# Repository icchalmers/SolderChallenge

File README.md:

# Solder Challenge

The Solder Challenge is a derivative of the [Solder Challenge by Rick Pennen](https://workspace.circuitmaker.com/Projects/Details/Rick-Pannen/Soldering-Challenge).
It's been updated to favour surface mount components and tweaked to parts I could easily source on RS.

# Licence

The project is currently licensed under a CC BY-NC-SA licence, as per the original project. Hopefully I'll get permission to remove the NC clause from the original author.

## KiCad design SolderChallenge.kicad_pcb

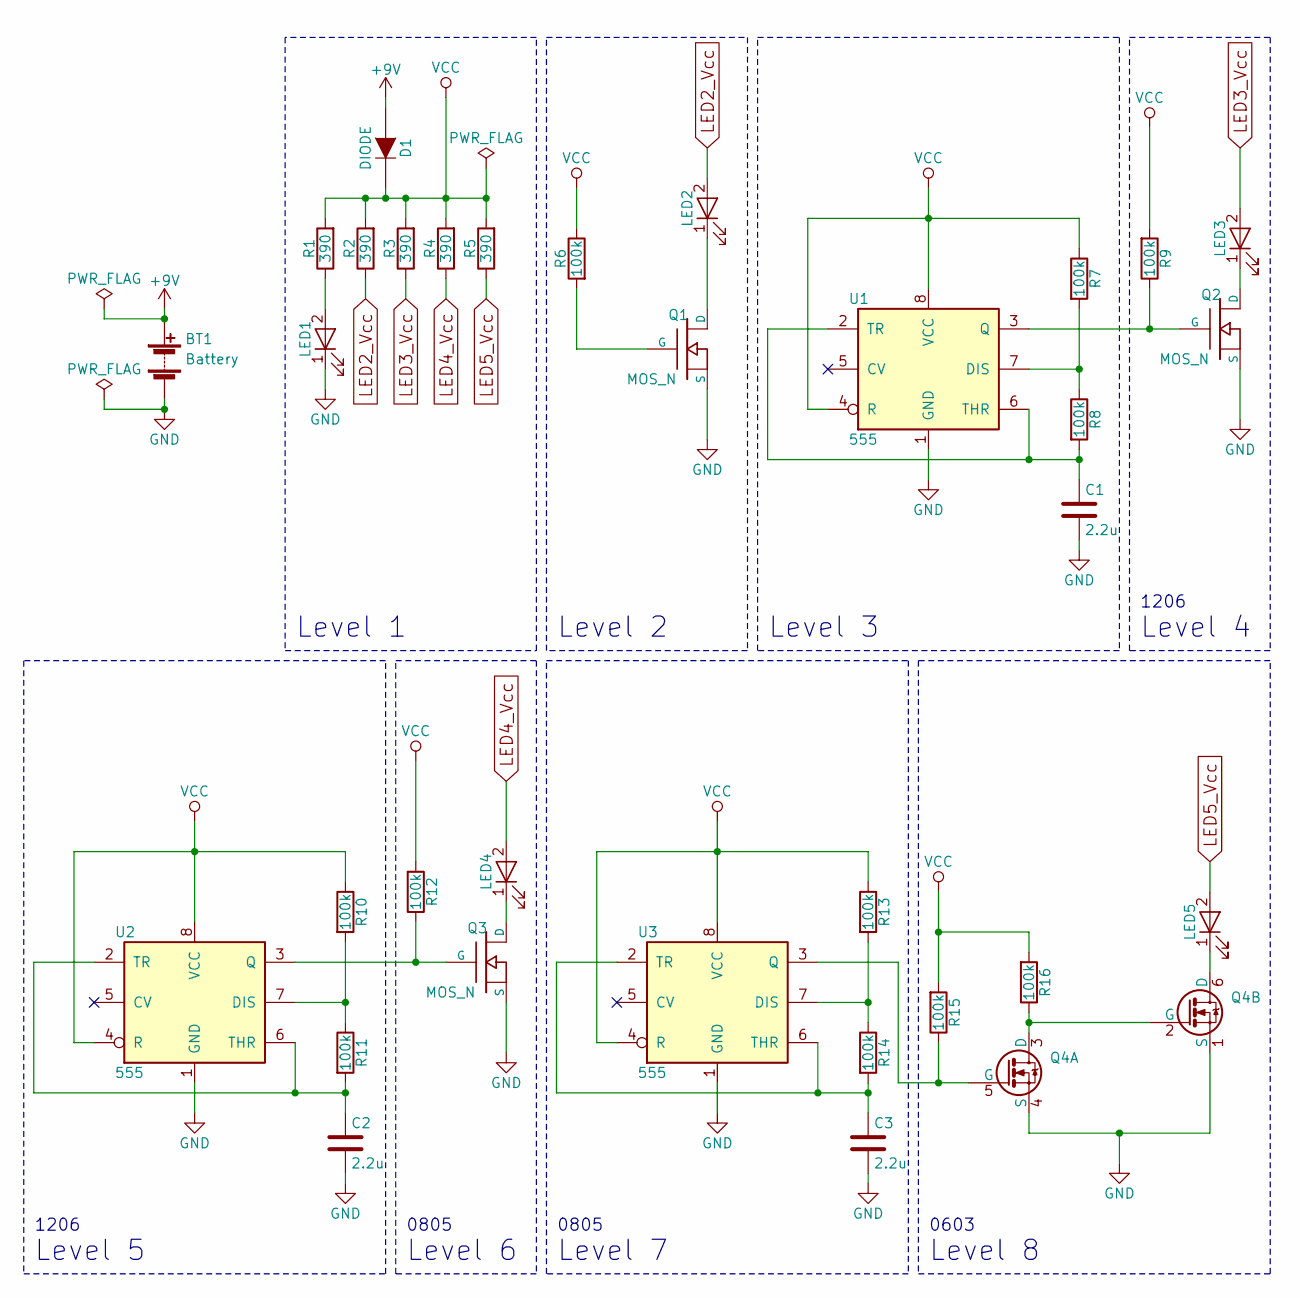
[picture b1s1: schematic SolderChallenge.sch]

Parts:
BT1: Battery; 9V_bat_press_contact
C1: 2.2u; C_Disc_D5.1mm_W3.2mm_P5.00mm
C2: 2.2u; C_1206_HandSoldering
C3: 2.2u; C_0805_HandSoldering
D1: DIODE; D_DO-41_SOD81_P7.62mm_Horizontal
LED1: LED; LED_D5.0mm
LED2: LED; LED_D3.0mm
LED3: LED; LED_PLCC-2
LED4: LED; LED_0805_HandSoldering
LED5: LED; LED_0603_HandSoldering
Q1: MOS_N; TO-92_Inline_Wide_SGD
Q2: MOS_N; SOT-23_GSD_Handsoldering
Q3: MOS_N; SOT-23_GSD_Nexperia_TO-236AB
Q4: MOS_N_x2; SOT-363_SC-70-6
R1, R2, R3, R4, R5: 390; R_Axial_DIN0207_L6.3mm_D2.5mm_P9.00mm_Horizontal
R6, R7, R8: 100k; R_Axial_DIN0204_L3.6mm_D1.6mm_P5.08mm_Horizontal
R9, R10, R11: 100k; R_1206_HandSoldering
R12, R13, R14: 100k; R_0805_HandSoldering
R15, R16: 100k; R_0603_HandSoldering
U1: 555; DIP-8_W7.62mm
U2: 555; SOIC-8_3.9x4.9mm_Pitch1.27mm
U3: 555; TSSOP-8_4.4x3mm_Pitch0.65mm

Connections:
+9V: BT1.1 (+), D1.A
GND: BT1.2 (-), C1.2, C2.2, C3.2, LED1.1 (K), Q1.S, Q2.S, Q3.S, Q4.1 (S), Q4.4 (S), U1.1 (GND), U2.1 (GND), U3.1 (GND)
LED2_Vcc: LED2.2 (A), R2.1
LED3_Vcc: LED3.2 (A), R3.1
LED4_Vcc: LED4.2 (A), R4.1
LED5_Vcc: LED5.2 (A), R5.1
unnamed: C1.1, R8.2, U1.2 (TR), U1.6 (THR)
unnamed: C2.1, R11.2, U2.2 (TR), U2.6 (THR)
unnamed: C3.1, R14.2, U3.2 (TR), U3.6 (THR)
unnamed: LED1.2 (A), R1.1
unnamed: LED2.1 (K), Q1.D
unnamed: LED3.1 (K), Q2.D
unnamed: LED4.1 (K), Q3.D
unnamed: LED5.1 (K), Q4.6 (D)
unnamed: Q1.G, R6.2
unnamed: Q2.G, R9.1, U1.3 (Q)
unnamed: Q3.G, R12.1, U2.3 (Q)
unnamed: Q4.2 (G), Q4.3 (D), R16.1
unnamed: Q4.5 (G), R15.1, U3.3 (Q)
unnamed: R7.2, R8.1, U1.7 (DIS)
unnamed: R10.2, R11.1, U2.7 (DIS)
unnamed: R13.2, R14.1, U3.7 (DIS)
VCC: D1.C, R1.2, R2.2, R3.2, R4.2, R5.2, R6.1, R7.1, R9.2, R10.1, R12.2, R13.1, R15.2, R16.2, U1.4 (R), U1.8 (VCC), U2.4 (R), U2.8 (VCC), U3.4 (R), U3.8 (VCC)

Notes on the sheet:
Level 1
Level 2
Level 3
Level 4
Level 5
Level 6
Level 7
Level 8
1206
0805
0603

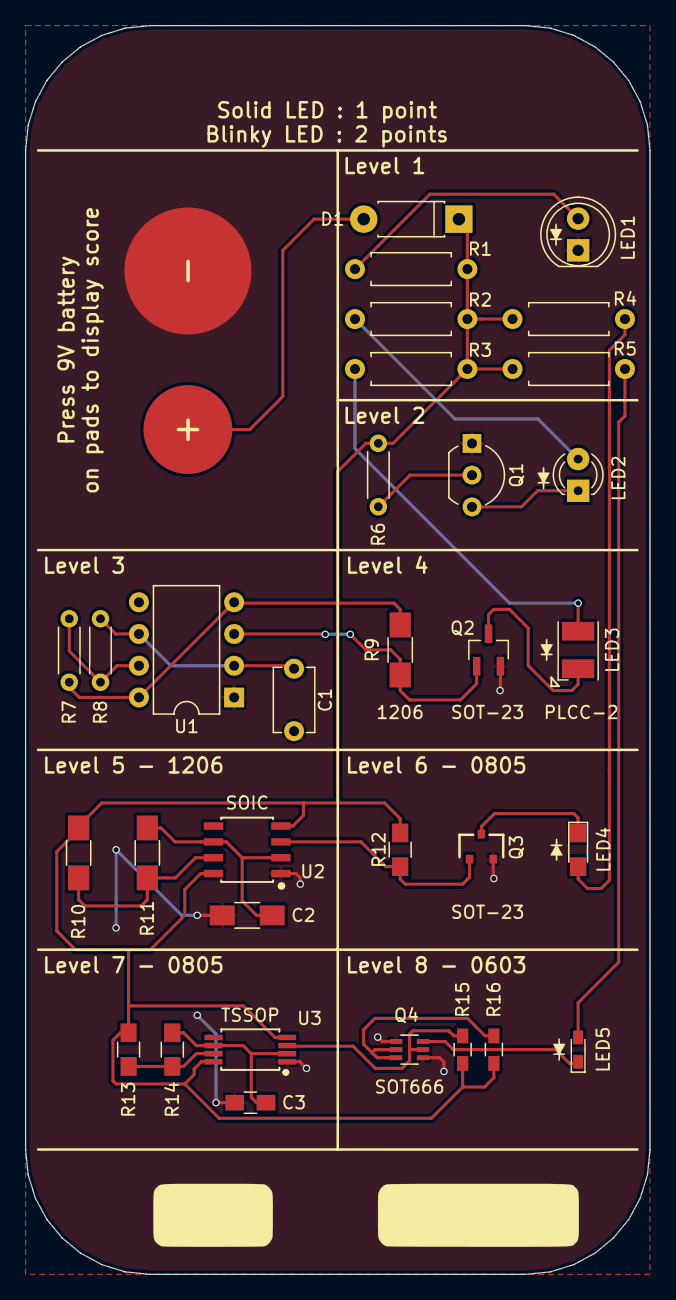
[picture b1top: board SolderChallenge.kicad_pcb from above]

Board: 2 copper layers, 50.0 x 100.0 mm, 33 parts (0 on the bottom side), 23 nets.

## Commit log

2018-07-19 Adding CC BY-NC-SA license, as per original Solder Challenge
2018-07-19 Inital commit
2018-07-19 Remove .txt extension so markdown on github works
2018-07-19 Add .md for markdown support...
2018-07-19 Removed battery label to make things look neater
2018-07-19 Move resistor labels for clarity
2018-07-19 Switch R4 and R5 for better routing
2018-07-20 Add PCB render
2018-07-20 Added diode polarity to silkscreen and made all LEDs have cathode at bottom
2018-07-23 Modified Q1 to use wide variant of package as that's what I ordred. RS had wrong info on site.
2018-07-23 Added gerbers
2018-07-24 Adding pdf of schematic
2018-07-25 Fixed silkscreen markings for pin 1 on U2 and U2. The dot on the silkscreen was implemented as an unnamed pin in the footprint, that only had silkscreen. This displayed fine, but wasn't exported in t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
2018-07-25 Add name, rev and github URL to back silkscreen
2018-07-25 Change Q3 to SOT-23 in place of SOT-323. The difference is that the Q3 footprint uses the recommended solder footprint, whereas Q2 uses the KiCAD hand solder footprint. Should be a good example of us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
2018-07-25 Change C1 to non polarised. Pops would have been fun if people soldered it in round the wrong way, but health and safety prevails over fun :(
2018-07-25 Switch orientation of one LED to force people to think about orientation. This is to make people more orientation aware without risking an exploding electrolytic in the face
2018-07-25 Regenerate gerbers for new layout
2018-07-25 Disable removal of silkscreen on pads. That's why the pin 1 marker on U2 and U3 footprints wasn't exprting to the gerbers. Using the non-pad based approach is still best option.
2018-07-25 Update render to match layout
2018-07-25 Forgot to update schematic footprints when I changed them in the layout. I wish KiCAD would automatically back-annotate, or at least let you choose to
2018-08-14 Fix diode polarity. The KiCAD library had the silkscreen wrong. I changed pin numbers to letters A and C to avoid confusion
2018-08-14 Changed holes on LED 2 from 0.9 mm to 0.7 mm. The holes were way too big for the LED I was using. Actually made it hard to solder
2018-08-14 Reduce hole size from 1.1 mm to 1.0 mm on diode. Excessively large holes made soldering harder
2018-08-14 Increase pin spacing on R1-5. Originally used 7.68mm. Increase to 9mm to make insertion easier
2018-08-14 Tighten up silkscreen on 1206 resistors. Should make alignment a bit easier
2018-08-14 Forgot to add new part to library
2018-08-14 Tweak 0603 LED footprint
2018-08-14 Add a corner mark on silkscreen for LED 3
2018-08-14 Reduce pad size on Q2 SOT-23 hand solder package. Pads were so long it made alignment harder, and were unnecessarily wide
2018-08-14 Decrease pad length on Q4, SOT-666. Long pads made it harder to align
2018-08-14 Added a name box on back silkscreen
2018-08-14 Add 'JLCJLCJLCJLC' placement to allow JLCPCB to place order number at right place on board
2018-08-14 Move order number placement label to back silkscreen
2018-08-14 Update gerbers
2018-08-14 Update zip of gerbers
2018-08-27 Update gerbers. Guess who re-sent V1 to the fabhouse a 2nd time...
2018-08-27 Moved C1 silk
2018-09-14 Add manufacturers part number to schematic symbols
2018-09-14 Add interactive BOM generated with InteractiveHtmlBom
2018-11-08 Forgot a few size labels
